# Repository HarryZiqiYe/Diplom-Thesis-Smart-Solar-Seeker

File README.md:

# Smart-Solar-Seeker

### Abstract

The paper hand in deals with the tracking of the sun, which follows the position of the sun, to get the maximum efficiency. Solar technology is a renewable energy source, that contributes to a sustainable environment. In contrast to flat lying solar panels, it is possible to produce more energy through tracking. A prototype has been developed and constructed which performs mostly all our tasks that we need.

Most of the mechanical components are standard aluminum profiles which are mainly used for the framework of our system, which can withstand weather and physical influences.
Furthermore, the project covers the implementation of a control algorithm on a microcontroller.
An GPS unit and light sensors have been used, which represents the input data of our algorithm. Two actuators, which have been installed, are controlled by the algorithm which are supposed to bring the solar panel to the the best solar radiation. The group compares with the measurements taken how economical it is to track and if it is necessary to rotate on two axes. An ESP32 microcontroller is used in the project and programmed with C++. Some circuit boards have been designed and implanted for our regulation of the supply voltage and for control of actuators, which uses inductors, relays, resistors, and other specific electronical components.

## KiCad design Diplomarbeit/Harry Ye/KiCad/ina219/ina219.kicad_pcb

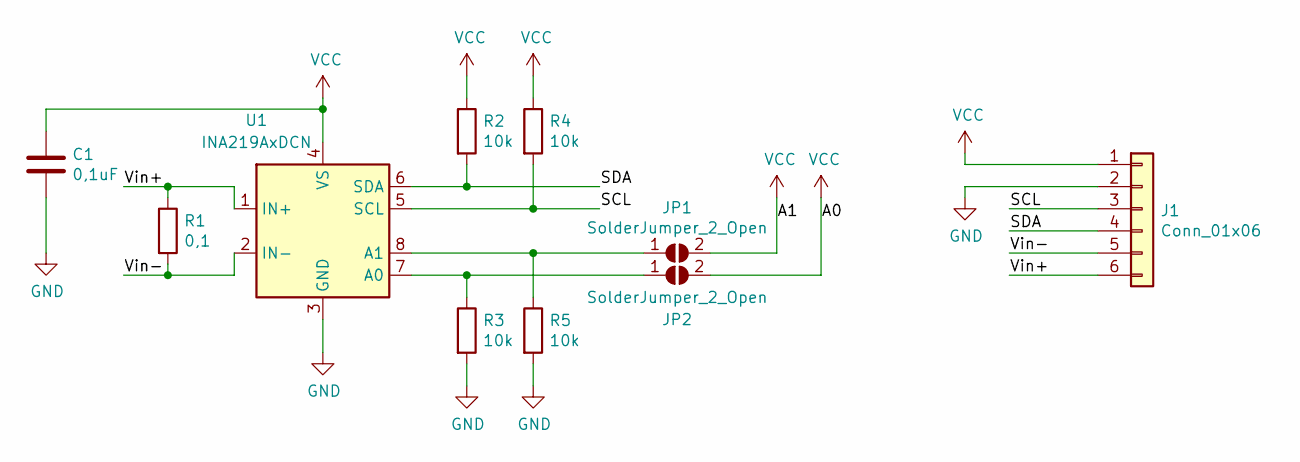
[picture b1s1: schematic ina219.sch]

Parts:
C1: 0,1uF; C_1206_3216Metric
J1: Conn_01x06; JST_EH_B6B-EH-A_1x06_P2.50mm_Vertical
JP1, JP2: SolderJumper_2_Open; SolderJumper-2_P1.3mm_Open_Pad1.0x1.5mm
R1: 0,1; R_2512_6332Metric
R2, R3, R4, R5: 10k; R_1206_3216Metric
U1: INA219AxDCN; SOT-23-8

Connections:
/SCL: J1.3, R4.2, U1.5 (SCL)
/SDA: J1.4, R2.2, U1.6 (SDA)
/Vin+: J1.6, R1.1, U1.1 (IN+)
/Vin-: J1.5, R1.2, U1.2 (IN-)
GND: C1.2, J1.2, R3.2, R5.2, U1.3 (GND)
unnamed: JP1.1 (A), R5.1, U1.8 (A1)
unnamed: JP2.1 (A), R3.1, U1.7 (A0)
VCC: C1.1, J1.1, JP1.2 (B), JP2.2 (B), R2.1, R4.1, U1.4 (VS)

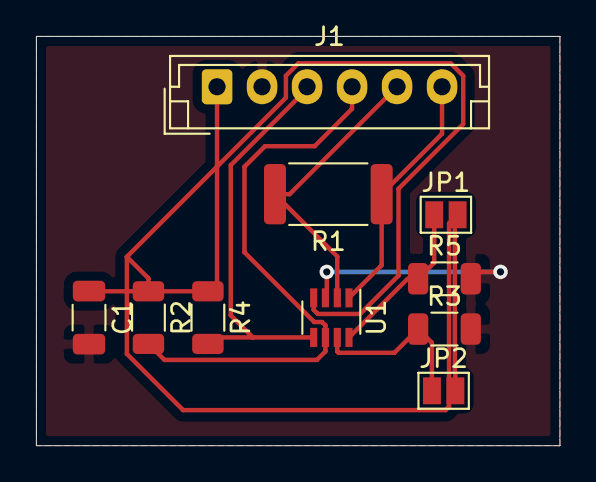
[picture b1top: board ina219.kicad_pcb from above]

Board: 2 copper layers, 29.1 x 22.7 mm, 10 parts (0 on the bottom side), 8 nets.

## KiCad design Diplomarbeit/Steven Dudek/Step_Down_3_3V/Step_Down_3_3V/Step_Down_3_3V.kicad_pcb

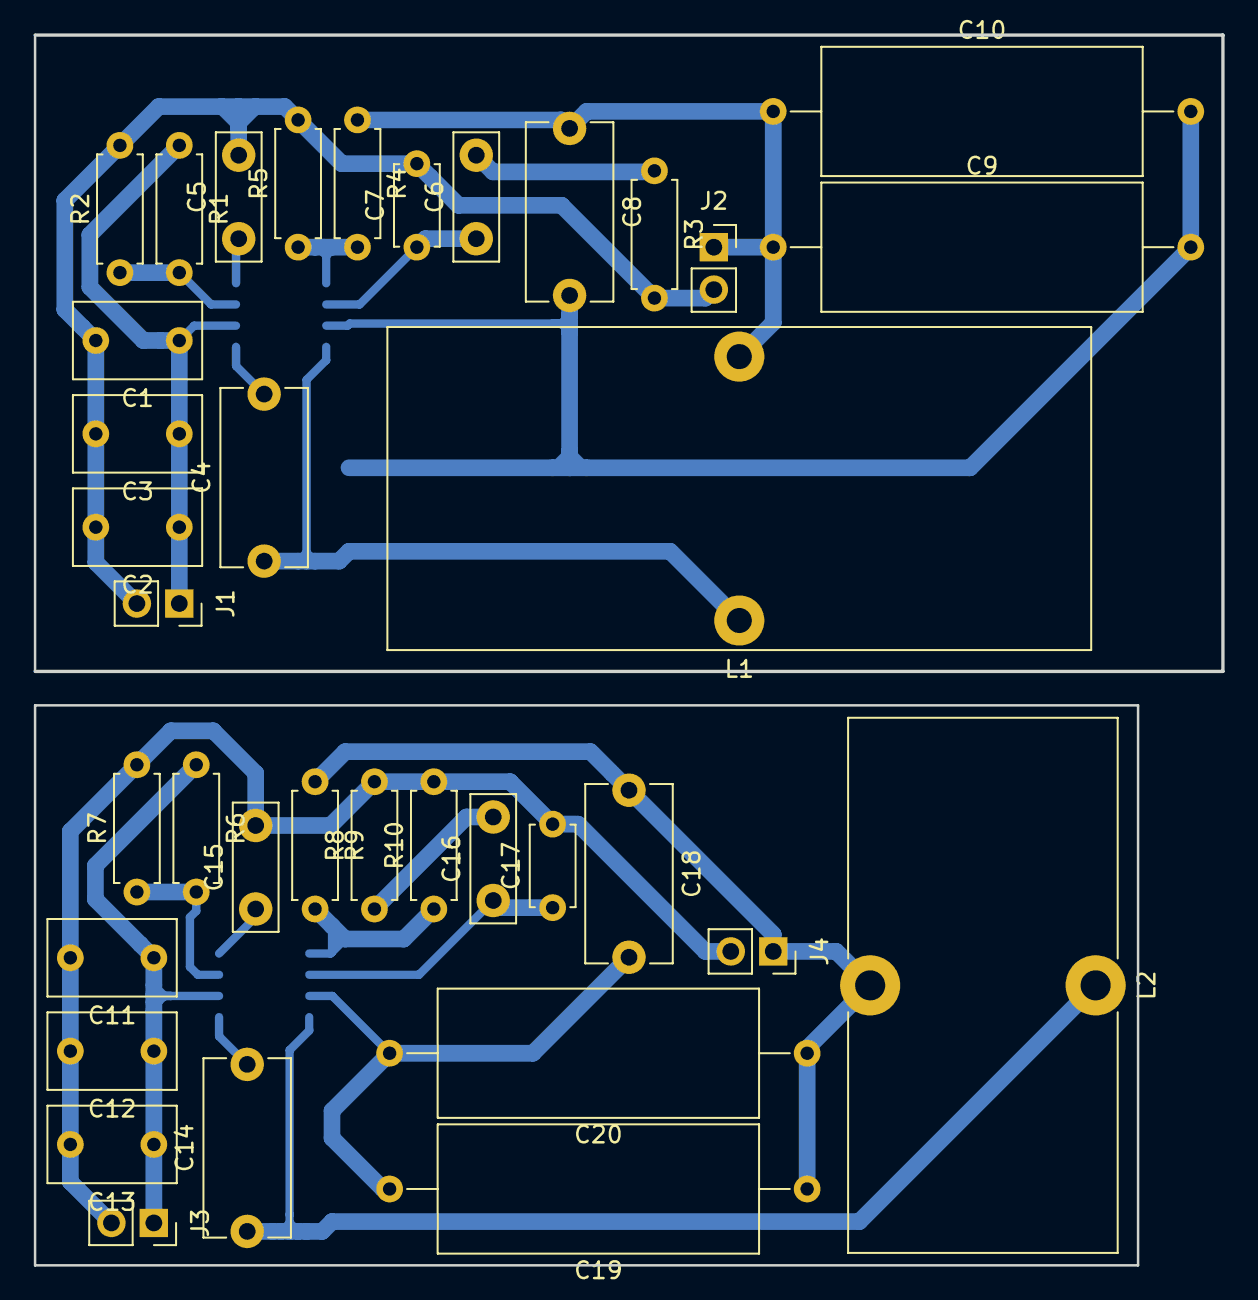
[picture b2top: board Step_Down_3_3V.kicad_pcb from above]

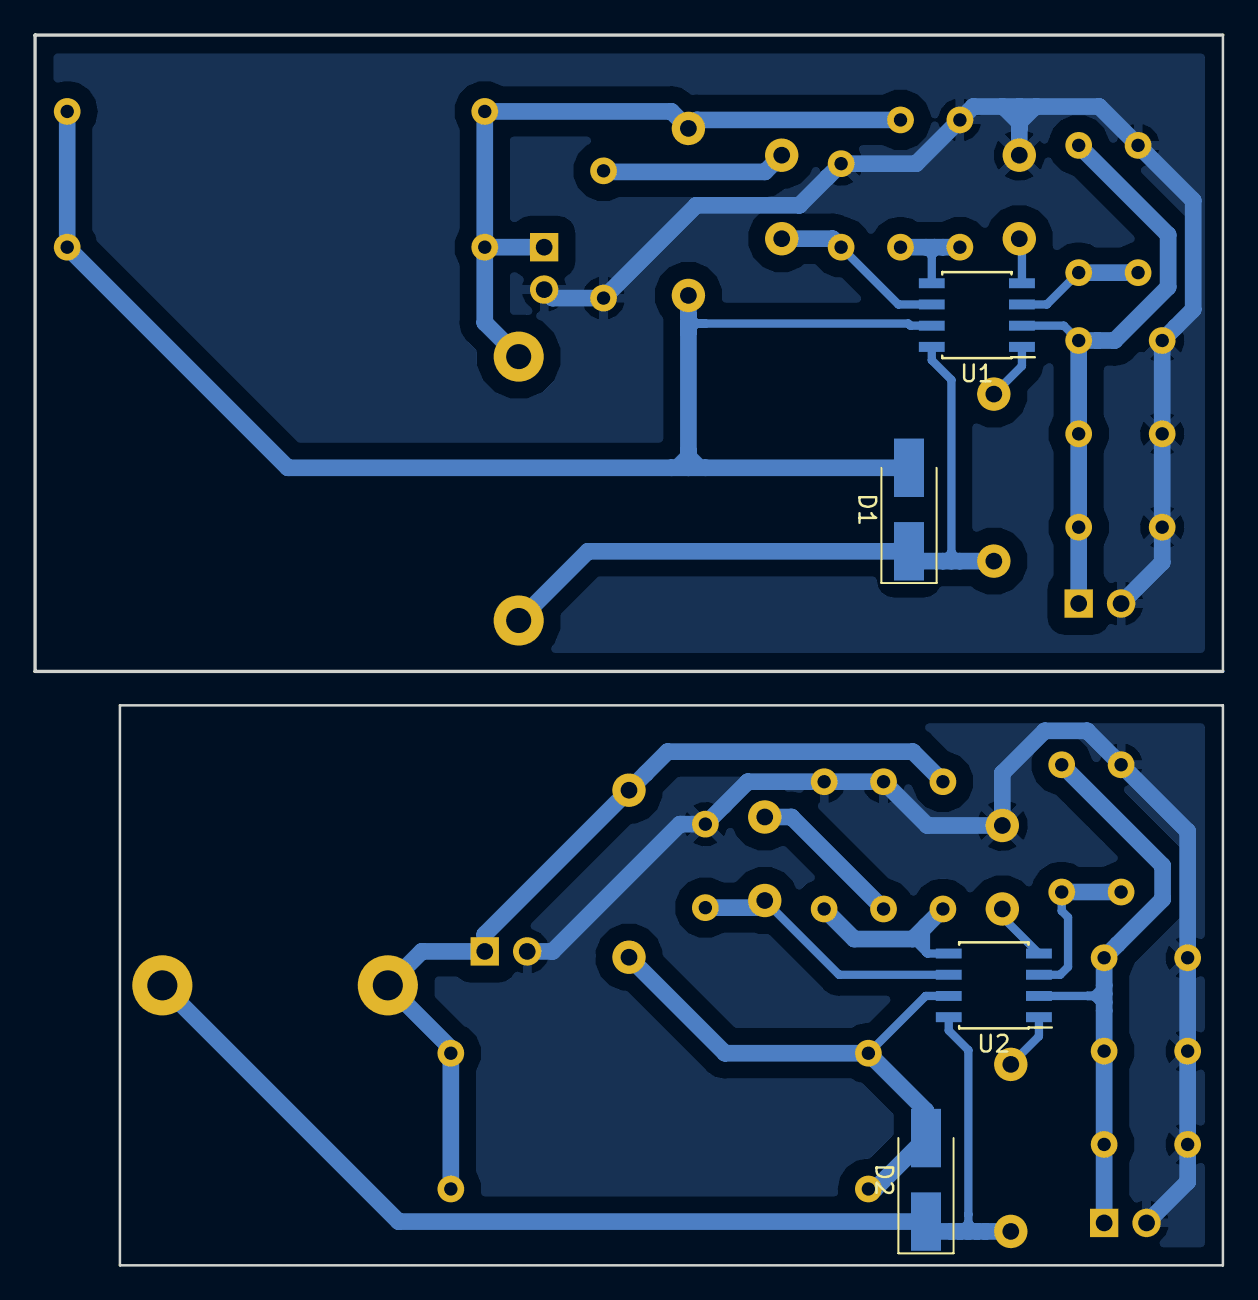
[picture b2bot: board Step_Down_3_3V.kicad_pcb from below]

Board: 2 copper layers, 71.1 x 73.6 mm, 40 parts (4 on the bottom side), 21 nets.

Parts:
C1, C2, C3, C11, C12, C13: 4.7µF; C_Disc_D7.5mm_W4.4mm_P5.00mm
C4, C8, C14, C18: 0.1µF; C_Disc_D10.5mm_W5.0mm_P10.00mm
C5, C15: 0.01µF; C_Disc_D7.5mm_W2.5mm_P5.00mm
C6, C16: 1000pF; C_Disc_D7.5mm_W2.5mm_P5.00mm
C7, C17: 47pF; C_Disc_D4.7mm_W2.5mm_P5.00mm
C9, C10, C19, C20: 47µF; C_Axial_L19.0mm_D7.5mm_P25.00mm_Horizontal
D1, D2: B340A; D_SMA_Handsoldering
J1, J2, J3, J4: Conn_01x02_Female; PinSocket_1x02_P2.54mm_Vertical
L1: 22µH; L_Toroid_Vertical_L41.9mm_W19.1mm_P15.80mm_Vishay_TJ7
L2: 12µH; L_Toroid_Vertical_L31.8mm_W15.9mm_P13.50mm_Bourns_5700
R1, R6: 332k; R_Axial_DIN0207_L6.3mm_D2.5mm_P7.62mm_Horizontal
R2, R7: 68.1k; R_Axial_DIN0207_L6.3mm_D2.5mm_P7.62mm_Horizontal
R3, R8: 29.4k; R_Axial_DIN0207_L6.3mm_D2.5mm_P7.62mm_Horizontal
R4, R9: 10.2k; R_Axial_DIN0207_L6.3mm_D2.5mm_P7.62mm_Horizontal
R5, R10: 3.24k; R_Axial_DIN0207_L6.3mm_D2.5mm_P7.62mm_Horizontal
U1, U2: TPS54331; SOIC-8_3.9x4.9mm_P1.27mm

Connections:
GND: C1.2, C2.2, C3.2, C5.2, C7.2, C11.2, C12.2, C13.2, C15.2, C17.2, J1.2, J2.2, J3.2, J4.2, R2.2, R3.2, R5.2, R7.2, R8.2, R10.2
unnamed: C1.1, C2.1, C3.1, J1.1, R1.1, U1.2
unnamed: C4.1, D1.1, L1.1, U1.8
unnamed: C4.2, U1.1
unnamed: C5.1, U1.4
unnamed: C6.1, C7.1, U1.6
unnamed: C6.2, R3.1
unnamed: C8.1, C9.1, C10.1, J2.1, L1.2, R4.1
unnamed: C8.2, C9.2, C10.2, D1.2, U1.7
unnamed: C11.1, C12.1, C13.1, J3.1, R6.1, U2.2
unnamed: C14.1, D2.1, L2.1, U2.8
unnamed: C14.2, U2.1
unnamed: C15.1, U2.4
unnamed: C16.1, C17.1, U2.6
unnamed: C16.2, R8.1
unnamed: C18.1, C19.1, C20.1, J4.1, L2.2, R9.1
unnamed: C18.2, C19.2, C20.2, D2.2, U2.7
unnamed: R1.2, R2.1, U1.3
unnamed: R4.2, R5.1, U1.5
unnamed: R6.2, R7.1, U2.3
unnamed: R9.2, R10.1, U2.5

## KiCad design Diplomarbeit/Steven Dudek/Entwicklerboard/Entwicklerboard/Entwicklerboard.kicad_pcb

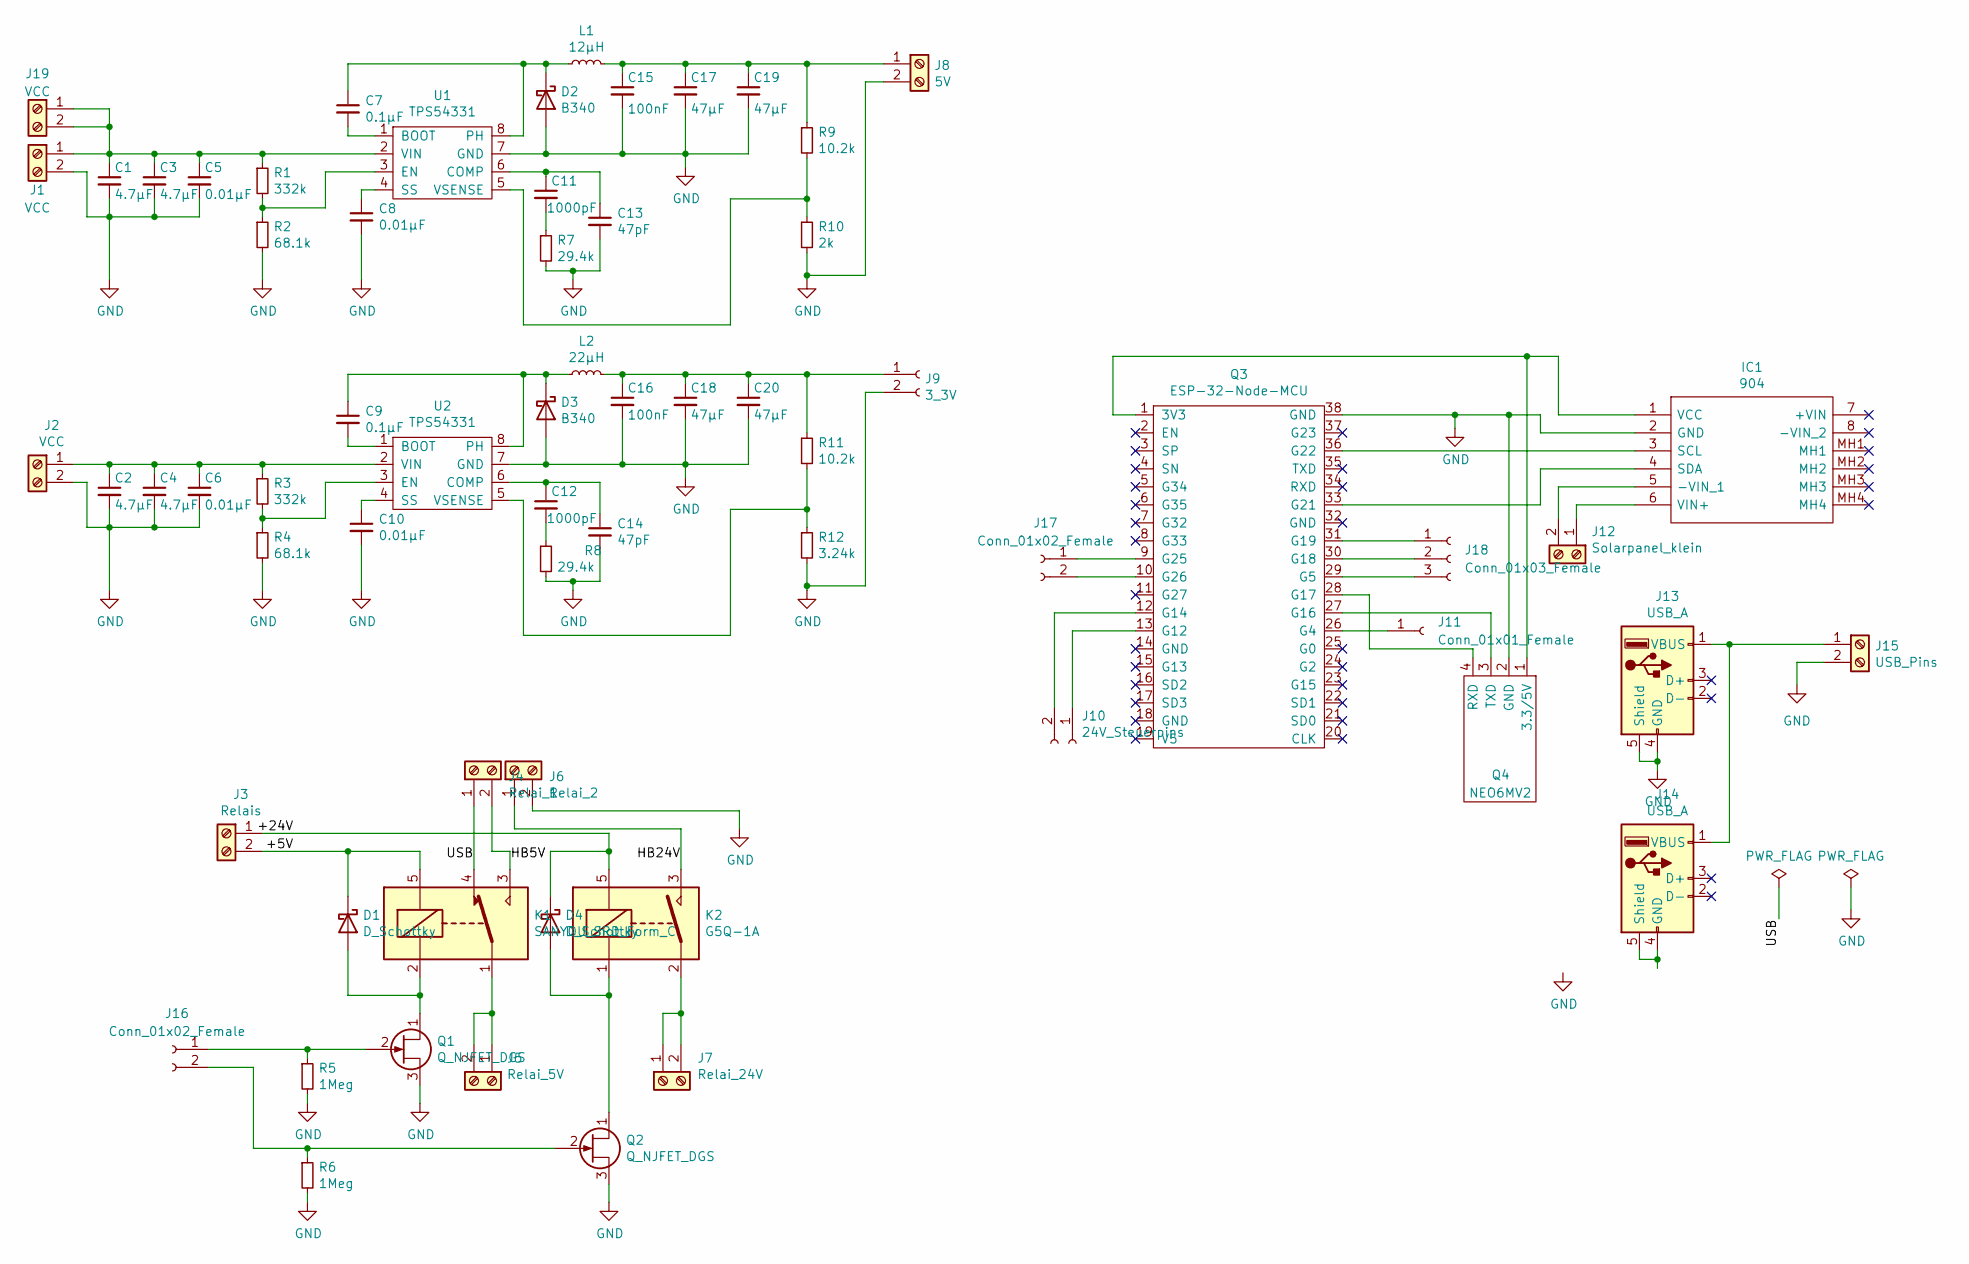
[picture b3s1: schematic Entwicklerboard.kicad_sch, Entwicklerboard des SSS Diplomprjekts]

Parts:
C1, C2, C3, C4: 4.7µF; C_1210_3225Metric_Pad1.42x2.65mm_HandSolder
C5, C6, C8, C10: 0.01µF; C_1206_3216Metric_Pad1.42x1.75mm_HandSolder
C7, C9: 0.1µF; C_1206_3216Metric_Pad1.42x1.75mm_HandSolder
C11, C12: 1000pF; C_1206_3216Metric_Pad1.42x1.75mm_HandSolder
C13, C14: 47pF; C_1206_3216Metric_Pad1.42x1.75mm_HandSolder
C15, C16: 100nF; C_1206_3216Metric_Pad1.42x1.75mm_HandSolder
C17, C18, C19, C20: 47µF; EEETC1V470P
D1, D4: D_Schottky; D_SMB_Handsoldering
D2, D3: B340; D_SMC
IC1: 904; Manufacturer_Part_Number 904
J1, J2, J19: VCC; TerminalBlock_Phoenix_MKDS-1,5-2-5.08_1x02_P5.08mm_Horizont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
J3: Relais; TerminalBlock_Phoenix_MKDS-1,5-2-5.08_1x02_P5.08mm_Horizont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
J4: Relai_1; TerminalBlock_Phoenix_MKDS-1,5-2-5.08_1x02_P5.08mm_Horizont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
J5: Relai_5V; TerminalBlock_Phoenix_MKDS-1,5-2-5.08_1x02_P5.08mm_Horizont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
J6: Relai_2; TerminalBlock_Phoenix_MKDS-1,5-2-5.08_1x02_P5.08mm_Horizont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
J7: Relai_24V; TerminalBlock_Phoenix_MKDS-1,5-2-5.08_1x02_P5.08mm_Horizont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
J8: 5V; TerminalBlock_Phoenix_MKDS-1,5-2-5.08_1x02_P5.08mm_Horizont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
J9: 3_3V; PinSocket_1x02_P2.54mm_Vertical
J10: 24V_Steuerpins; PinSocket_1x02_P2.54mm_Vertical
J11: Conn_01x01_Female; PinSocket_1x01_P2.54mm_Vertical
J12: Solarpanel_klein; TerminalBlock_Phoenix_MKDS-1,5-2-5.08_1x02_P5.08mm_Horizont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
J13, J14: USB_A; USB_A_CNCTech_1001-011-01101_Horizontal
J15: USB_Pins; TerminalBlock_Phoenix_MKDS-1,5-2-5.08_1x02_P5.08mm_Horizont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
J16, J17: Conn_01x02_Female; PinSocket_1x02_P2.54mm_Vertical
J18: Conn_01x03_Female; PinSocket_1x03_P2.54mm_Vertical
K1: SANYOU_SRD_Form_C; Relay_SPDT_SANYOU_SRD_Series_Form_C
K2: G5Q-1A; Relay_SPST_Omron-G5Q-1A
L1: 12µH; L_Toroid_Vertical_L31.8mm_W15.9mm_P13.50mm_Bourns_5700
L2: 22µH; L_Toroid_Vertical_L41.9mm_W19.1mm_P15.80mm_Vishay_TJ7
Q1, Q2: Q_NJFET_DGS; TO-220-3_Vertical
Q3: ESP-32-Node-MCU; ESP32-NodeMCU
Q4: NEO6MV2; GY-NEO6MV2
R1, R3: 332k; R_1206_3216Metric_Pad1.42x1.75mm_HandSolder
R2, R4: 68.1k; R_1206_3216Metric_Pad1.42x1.75mm_HandSolder
R5, R6: 1Meg; R_MiniMELF_MMA-0204
R7, R8: 29.4k; R_0805_2012Metric_Pad1.15x1.40mm_HandSolder
R9, R11: 10.2k; R_MiniMELF_MMA-0204
R10: 2k; R_1206_3216Metric_Pad1.42x1.75mm_HandSolder
R12: 3.24k; R_1206_3216Metric_Pad1.42x1.75mm_HandSolder
U1, U2: TPS54331; NE555DR

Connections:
/+5V: D1.1 (K), J3.2, K1.5
/+24V: D4.1 (K), J3.1, K2.5
/HB5V: J4.2, K1.3
/HB24V: J6.1, K2.3
/USB: J4.1, K1.4
unnamed: C1.1, C3.1, C5.1, J1.1, J19.1, J19.2, R1.1, U1.2 (VIN)
unnamed: C2.1, C4.1, C6.1, J2.1, R3.1, U2.2 (VIN)
unnamed: C7.1, D2.1 (K), L1.1, U1.8 (PH)
unnamed: C7.2, U1.1 (BOOT)
unnamed: C8.1, U1.4 (SS)
unnamed: C9.1, D3.1 (K), L2.1, U2.8 (PH)
unnamed: C9.2, U2.1 (BOOT)
unnamed: C10.1, U2.4 (SS)
unnamed: C11.1, C13.1, U1.6 (COMP)
unnamed: C11.2, R7.1
unnamed: C12.1, C14.1, U2.6 (COMP)
unnamed: C12.2, R8.1
unnamed: C15.1, C17.1, C19.1, J8.1, L1.2, R9.1
unnamed: C16.1, C18.1, C20.1, J9.1, L2.2, R11.1
unnamed: D1.2 (A), K1.2, Q1.1 (D)
unnamed: D4.2 (A), K2.1, Q2.1 (D)
unnamed: IC1.1 (VCC), Q3.1 (3V3), Q4.1 (3.3/5V)
unnamed: IC1.3 (SCL), Q3.36 (G22)
unnamed: IC1.4 (SDA), Q3.33 (G21)
unnamed: IC1.5 (-VIN_1), J12.2
unnamed: IC1.6 (VIN+), J12.1
unnamed: J5.1, J5.2, K1.1
unnamed: J7.1, J7.2, K2.2
unnamed: J10.1, Q3.13 (G12)
unnamed: J10.2, Q3.12 (G14)
unnamed: J11.1, Q3.26 (G4)
unnamed: J13.1 (VBUS), J14.1 (VBUS), J15.1
unnamed: J16.1, Q1.2 (G), R5.1
unnamed: J16.2, Q2.2 (G), R6.1
unnamed: J17.1, Q3.9 (G25)
unnamed: J17.2, Q3.10 (G26)
unnamed: J18.1, Q3.31 (G19)
unnamed: J18.2, Q3.30 (G18)
unnamed: J18.3, Q3.29 (G5)
unnamed: Q3.27 (G16), Q4.3 (TXD)
unnamed: Q3.28 (G17), Q4.4 (RXD)
unnamed: R1.2, R2.1, U1.3 (EN)
unnamed: R3.2, R4.1, U2.3 (EN)
unnamed: R9.2, R10.1, U1.5 (VSENSE)
unnamed: R11.2, R12.1, U2.5 (VSENSE)

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
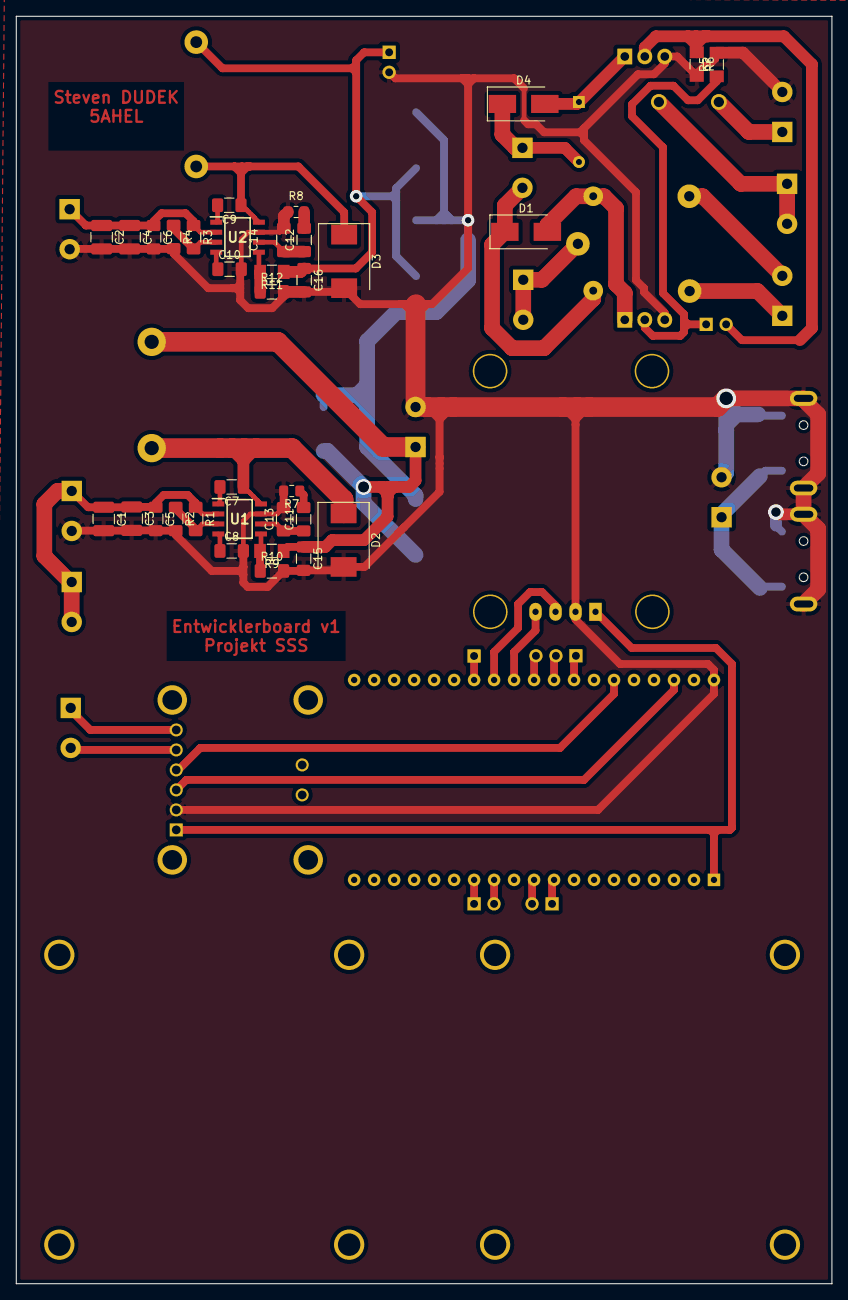
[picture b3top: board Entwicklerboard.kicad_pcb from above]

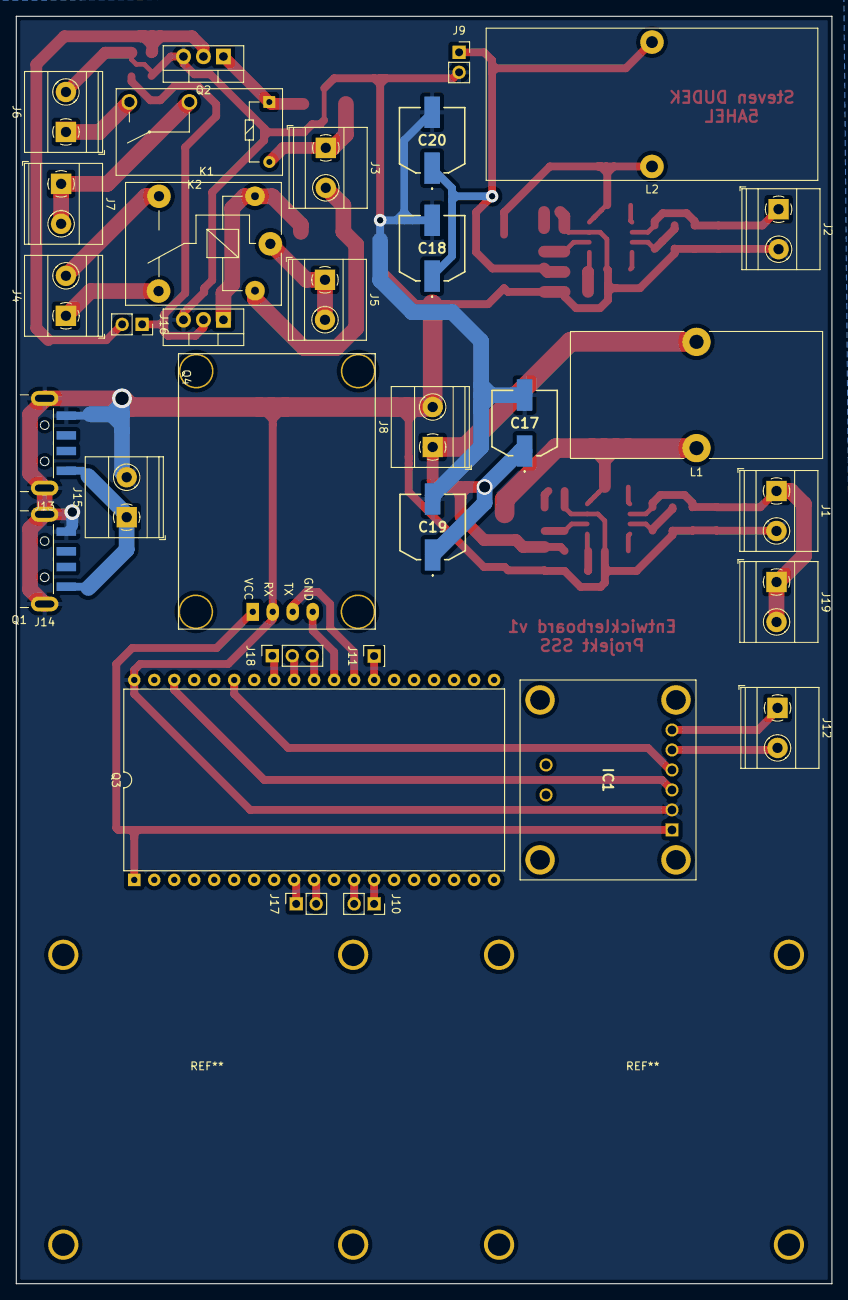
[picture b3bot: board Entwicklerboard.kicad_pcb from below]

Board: 2 copper layers, 103.6 x 161.0 mm, 66 parts (32 on the bottom side), 46 nets.

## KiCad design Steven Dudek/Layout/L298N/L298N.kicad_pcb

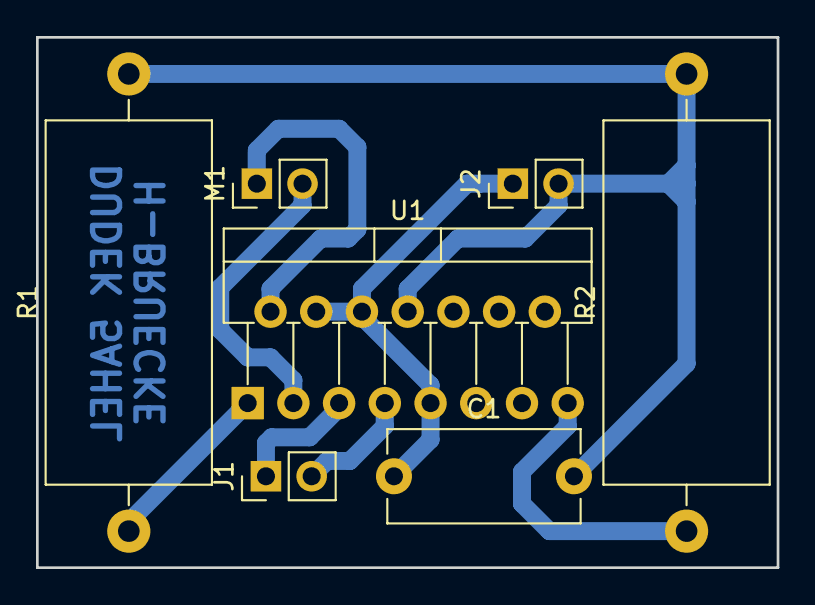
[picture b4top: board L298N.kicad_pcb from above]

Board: 2 copper layers, 41.1 x 29.5 mm, 7 parts (0 on the bottom side), 8 nets.

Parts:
C1: 100nF; C_Disc_D10.5mm_W5.0mm_P10.00mm
J1, J2: Conn_01x02_Female; PinHeader_1x02_P2.54mm_Vertical
M1: Motor_DC; PinHeader_1x02_P2.54mm_Vertical
R1, R2: 1; R_Axial_DIN0922_L20.0mm_D9.0mm_P25.40mm_Horizontal
U1: L298HN; TO-220-15_P2.54x2.54mm_StaggerOdd_Lead4.58mm_Vertical

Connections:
+5V: C1.1, J2.1, U1.4, U1.6, U1.9
/ESP_IN1: J1.1, U1.5
/ESP_IN2: J1.2, U1.7
GND: C1.2, J2.2, R1.2, R2.2, U1.8
unnamed: M1.1, U1.2
unnamed: M1.2, U1.3
unnamed: R1.1, U1.1
unnamed: R2.1, U1.15

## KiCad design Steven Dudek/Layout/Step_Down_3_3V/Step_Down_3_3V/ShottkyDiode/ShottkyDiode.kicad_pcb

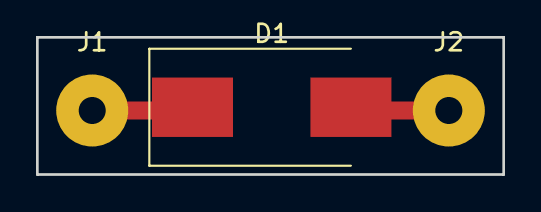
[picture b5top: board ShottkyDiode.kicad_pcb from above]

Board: 2 copper layers, 25.9 x 7.6 mm, 3 parts (0 on the bottom side), 2 nets.

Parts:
D1: B340; D_SMC_Handsoldering
J1, J2: Conn_01x01_Male; SolderWirePad_1x01_Drill1.5mm

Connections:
unnamed: D1.1, J1.1
unnamed: D1.2, J2.1

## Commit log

2021-09-09 Create Edis_Kereku (Software)
2021-09-09 Allgemeine Projektdateien
2021-09-29 Create test
2021-09-29 Create tets
2021-09-29 1st Upload
    29.09.2021
2021-10-27 2nd Upload
2022-01-24 3rd Upload
2022-01-24 4th Upload
2022-01-24 4th Upload
    StepDown24_5V.raw konnte nicht hochgeladen werden -> File zu groß
2022-01-25 Add files via upload
    GPS-Ausgabe Serial-Monitor
2022-01-25 Add files via upload
    Linearantrieb Motor testen
2022-01-25 Add files via upload
    Stromsensor Ausgabe
2022-01-25 Add files via upload
    Testcode für Motoransteuerung mit GPS-Daten
2022-03-24 Create Edis Kereku
2022-03-24 24.03.2022 Upload
2022-03-24 24.04.2022 Upload
2024-01-16 README.md
